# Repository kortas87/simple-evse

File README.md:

# NEWS #

**24.12.2014**

---

At the moment we are testing new sealed AC/DC converters which should replace the original black 12V 500mA power adapters. The greatest advantage is that these power supply units are small enough to fit in the connector J1772 easily (no need for pushing or changing anything) and they are more or less water resistant (please do not forget that in the connector there are usually other things as well which may cause short if too much of water gets in - e.g. relay contacts)

## Project introduction ##

We have developed a board based on PIC microcontroller which is able to generate 1kHz PWM signal, detect the vehicle and control the relay. It is also possible to adjust PWM width for current regulation. The board is small enough to be installed directly into J1772 Yazaki connector.

The kit can be obtained from [EV Power](http://www.ev-power.eu/index.php?cl=search&searchparam=EVSE) (Czech Republic).

  * [How to make your own J1772 connector with EVSE](SimpleEvseJ1772guide.md)
  * [J1772 button connection scheme](J1772buttonConnectionSchematic.md)
  * [Setting different charging current limit (6 - 20A)](HowToSetDifferentCurrentLimit.md)

# EVSE Kit includes #

1. Mounted PCB including microcontroller with latest [firmware](http://code.google.com/p/simple-evse/source/checkout)

2. 12V DC power supply

3. AC relay 230V 20A

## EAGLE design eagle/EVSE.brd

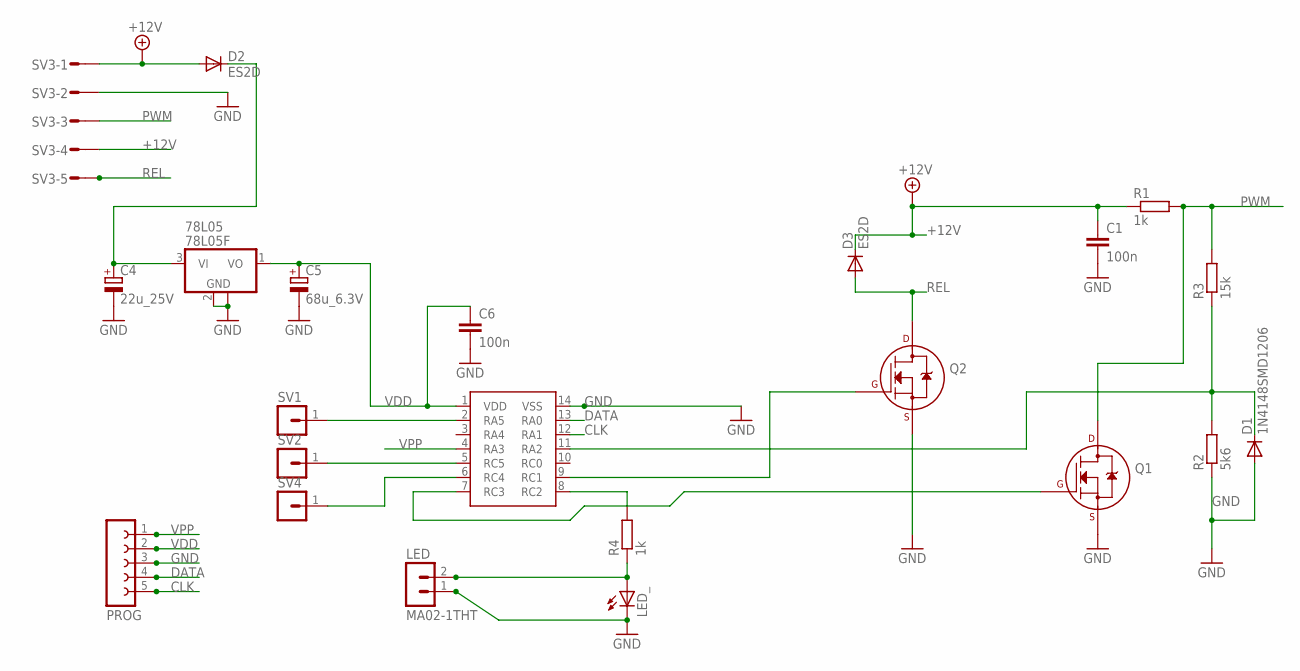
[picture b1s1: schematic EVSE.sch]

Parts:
78L05: 78L05F; SOT89
C1, C6: 100n; C0805
C4: 22u_25V; B/3528-21W
C5: 68u_6.3V; B/3528-21W
D1: 1N4148SMD1206; D1206
D2, D3: ES2D; SMB
LED: MA02-1THT; MA02-1
LED_: LEDSMT1206; 1206
PIC16F1825: PIC16F1825SOIC; SO-14
PROG: FE05-1
Q1, Q2: 2N7002_SOT23; SOT-23
R1, R4: 1k; R0805
R2: 5k6; R0805
R3: 15k; R0805
SV1, SV2, SV4: PIN-HEADER1
SV3: MT6-5

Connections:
+12V: C1.1, D2.A, D3.C, R1.1, SV3.1, SV3.4
CLK: PIC16F1825.12 (RA1), PROG.5
DATA: PIC16F1825.13 (RA0), PROG.4
GND: 78L05.2 (GND), 78L05.2@1 (GND), C1.2, C4.-, C5.-, C6.2, D1.A, LED.1, LED_.C, PIC16F1825.14 (VSS), PROG.3, Q1.2 (S), Q2.2 (S), R2.1, SV3.2
unnamed: 78L05.3 (VI), C4.+, D2.C
unnamed: D1.C, PIC16F1825.11 (RA2), R2.2, R3.1
unnamed: PIC16F1825.7 (RC3), Q1.1 (G)
unnamed: PIC16F1825.2 (RA5), SV1.1
unnamed: PIC16F1825.9 (RC1), Q2.1 (G)
unnamed: PIC16F1825.5 (RC5), SV2.1
unnamed: PIC16F1825.6 (RC4), SV4.1
unnamed: PIC16F1825.8 (RC2), R4.2
unnamed: LED.2, LED_.A, R4.1
PWM: Q1.3 (D), R1.2, R3.2, SV3.3
REL: D3.A, Q2.3 (D), SV3.5
VDD: 78L05.1 (VO), C5.+, C6.1, PIC16F1825.1 (VDD), PROG.2
VPP: PIC16F1825.4 (RA3), PROG.1

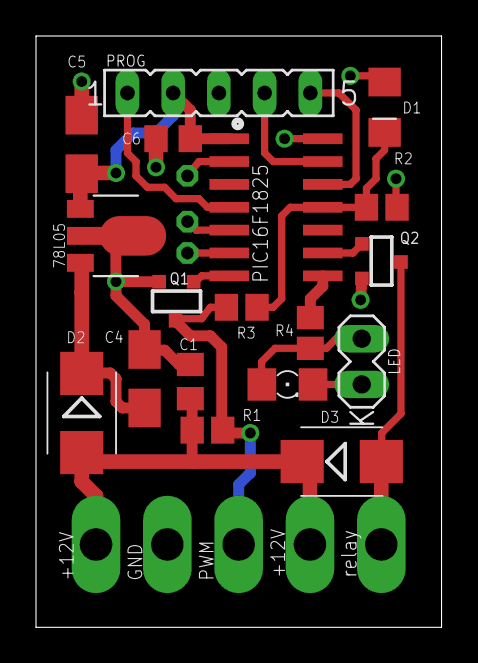
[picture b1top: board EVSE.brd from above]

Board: 2 copper layers, 22.5 x 32.9 mm, 22 parts (0 on the bottom side), 17 nets.

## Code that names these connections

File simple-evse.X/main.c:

/*
 * File:   main.c
 * Author: Petr Kortanek, i4wifi a.s.
 *
 * Created on 23rd November 2013
 *
 * 2014-01-11 - RA3 (MCLR, prog 1) input for button
 * 2014-04-09 - RA0 (ICSPDAT, prog 4) potentiometer input
 * 2014-08-11 - fixed PWM duty (+10bit), RA1 (ICSPCLK, prog 5) input switch 6A / 10A
 */

#include <stdio.h>
#include <stdlib.h>
#include <xc.h>

#define _XTAL_FREQ 4000000
#define Button_pressed PORTAbits.RA3

#pragma config LVP = OFF, MCLRE = OFF, BOREN = OFF, PLLEN = OFF, FOSC = INTOSC, WDTE = OFF, CP = OFF, PWRTE = OFF

char latcha = 0;
char latchc = 0;
char pilot_value = 255;
char pot_value = 255;
char pot_value2 = 255;
char adchannel = 2;
char measure_nth = 0;
char button_pressed_counter = 0;
char amps = 16;
char amps_to_set = 16;
char setbypot = 0;
short duty = 500; //50%

//attached to RC1
void relayon() {
  latchc = latchc | 0b00000011;//RC1+backup RC0
  PORTC = latchc;
}
void relayoff() {
  latchc = latchc & 0b11111100;//RC1+backup RC0
  PORTC = latchc;
}

//attached to RC2
void ledon() {
  latchc = latchc | 0b00000100;
  PORTC = latchc;
}
void ledoff() {
  latchc = latchc & 0b11111011;
  PORTC = latchc;
}

void button_flashing() {
  for (int i=0; i<20; i++) {
    ledon();
    __delay_ms(30);
    ledoff();
    __delay_ms(30);
  }
}

void setAmps() {
  setbypot = 0;

  //we get current limit from the pot
  if (pot_value <= 222) { //<4.4V, amps 6-80
    amps = 6 + (222-pot_value)/3;
    setbypot = 1;
  }
  //we get current limit from the "pot2" (set 6A / 10A)
  if (pot_value2 <= 222) { //<4.4V,
    amps = 10;
    if (pot_value2 <= 25) { //short => amps 6 ~ >3kOhm
      amps = 6;
    }
    setbypot = 1;
  }
  if (setbypot == 0) {
    amps = amps_to_set;
  }
  //minimum
  if (amps < 5)
    amps = 5;
  //maximum
  if (amps > 80)
    amps = 80;
  
  //compute PWM duty
  if (amps < 51)
    duty = 1000 - (100 * amps) / 6;
  else
    duty = 1000 - (4*amps+640);

  //set PWM output 10bit
  CCPR1L = duty >> 2;
  duty &= 0b00000011;
  duty <<= 4;
  CCP1CON = duty + 12; //1100

}

void main() {

    OSCCON = 0b01101010; // 4MHz

    TRISA = 0b11111111; //pilot detect RA2, button detect RA3, pot RA0, pot2 RA1
    TRISC = 0b11110000; //relay RC1 (+backup RC0), LED RC2, pilot RC3
    latcha = 0;
    latchc = 0;
    PORTA = latcha;
    PORTC = latchc;

    ADCON1 = 0b01100000; // f/64 4MHz, 16 us
    ADON = 1; //channel: RA2=PWM detect, RA0=pot value, RA1=pot2 value
    ADCON0bits.CHS = 2;

    //pilot PWM RC3
    PSTR1CONbits.STR1C = 1;
    APFCON1bits.P1CSEL = 0; //P1C function is on RC3
    
    PR2 = 249 ;//period value
    CCP1CON = 0b00001100; //PWM mode

    OPTION_REG = 0b00000001; //pullups and TMR0
    WPUAbits.WPUA3 = 1; //button pressed detect - MCLR
    WPUAbits.WPUA1 = 1;  //6A / 10A input RA1

    //T2CON timer ON + prescaler 4
    T2CON = 0b00000101 ;

    //INTCON = 0b11100000;
    GIE = 1;
    PEIE = 1;
    
    ADIE = 1;
    TMR2IE = 1;
    
    setAmps();

    while(1) {

        //MODE set current
        if(Button_pressed == 0) {
          button_pressed_counter++;
          //setting mode entered - rapid led flashing
          if (button_pressed_counter == 5) {
            button_flashing();
            amps_to_set = 0;
          }
          if (button_pressed_counter >= 5) {
            amps_to_set++;
            setAmps();
            ledoff();
            __delay_ms(300);
            ledon();
            __delay_ms(300);
          } else {
            __delay_ms(800);
          }

        //MODE normal operation
        } else {
          if(button_pressed_counter>=5) {
            //current setting mode exit confirmation
            button_flashing();
          }
          button_pressed_counter = 0;

          //car connected (pilot pulled down <8V)
          if(pilot_value < 111) {
            relayon();
            ledon();
            __delay_ms(800);

          } else {
            ledon();
            __delay_ms(30);
            relayoff();
          }
          ledoff();
          __delay_ms(300);
        }
    }
}

void interrupt isr() {

  //channel: RA2=PWM detect or RA0=pot value
  if (ADIF) {
    if (adchannel == 0) {
      pot_value = ADRESH;
      setAmps();
      adchannel = 1;
    } else if (adchannel == 1) {
      pot_value2 = ADRESH;
      setAmps();
      adchannel = 2;
    } else   {
      pilot_value = ADRESH;
      adchannel = 0;
    }
    ADCON0bits.CHS = adchannel;
    ADIF = 0;
  }

  if (TMR2IF) {
    TMR2IF = 0;
    //voltage must be measured when voltage is "up"
    measure_nth++;
    if (measure_nth>98) {
      __delay_us(950);
      GO_nDONE = 1;
      measure_nth = 0;
    }
  }
}

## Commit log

2014-01-15 Initial commit.
2014-01-16 Directories update, added images, eagle scheme and board.
2014-01-16 Some files deleted.
2014-01-16 Files cleanup
2014-11-12 Changed sourcecode (current settings PWM fix, another ways of setting current)
2014-11-17 Updated board layout - cosmetic changes.
2015-05-26 Migrating wiki contents from Google Code
2015-05-26 ./finishGoogleCodeGitHubWikiMigration: Moved ProjectHome.md from wiki branch to README.md in master branch.
